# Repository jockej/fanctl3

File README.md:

# fanctl3
A simpler version of fanctl2

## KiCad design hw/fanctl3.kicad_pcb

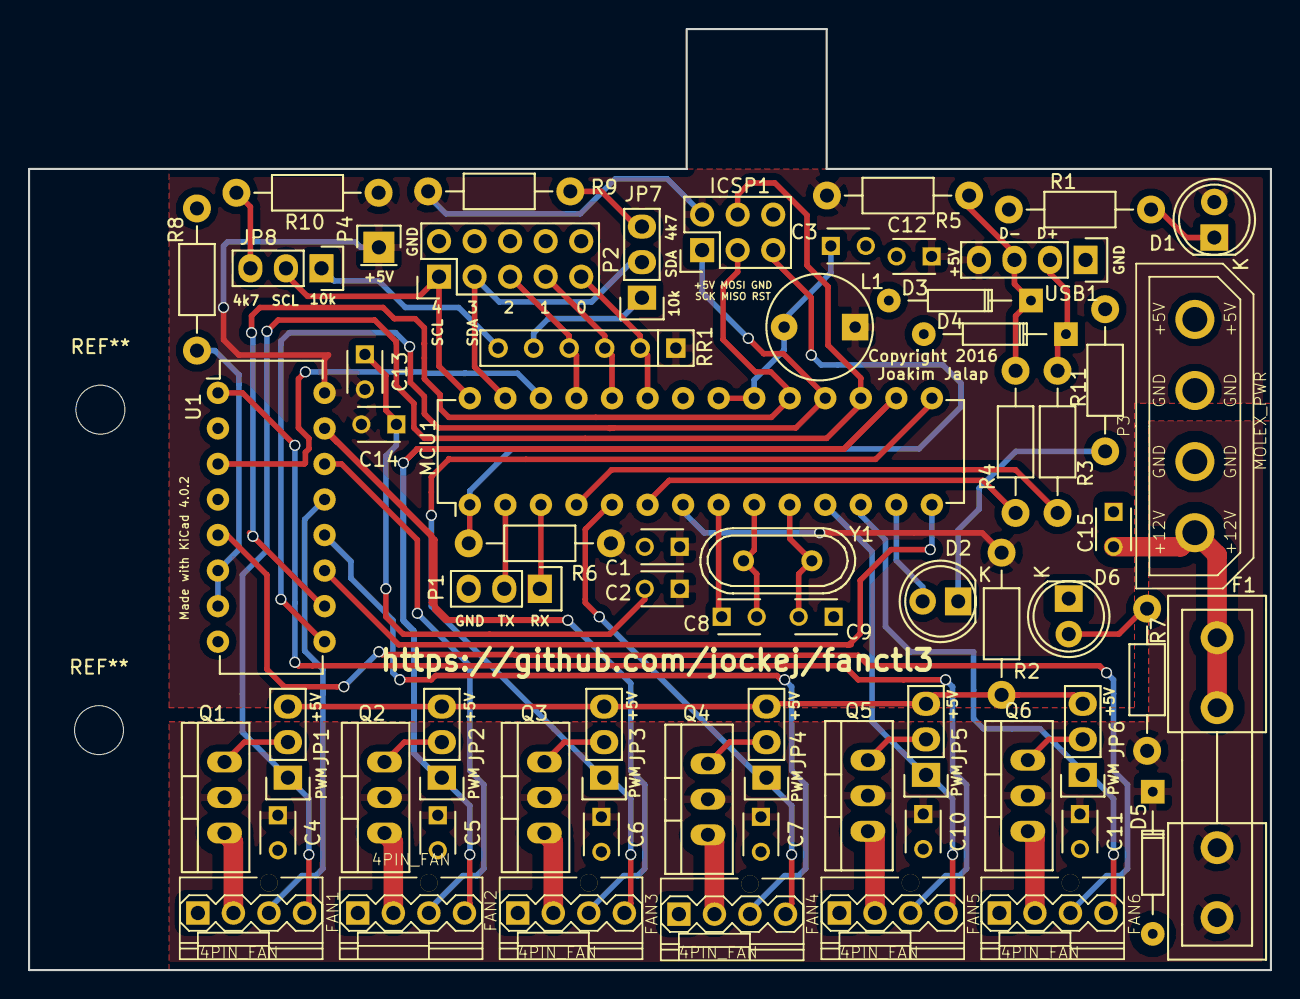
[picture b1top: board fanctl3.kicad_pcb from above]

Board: 2 copper layers, 88.8 x 67.2 mm, 64 parts (0 on the bottom side), 58 nets.

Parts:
C1, C3, C4, C5, C6, C7, C10, C11, C12, C13: 0.1u; C_Disc_D3_P2.5
C2, C14: 22n; C_Disc_D3_P2.5
C8, C9: 22p; C_Disc_D3_P2.5
C15: Decoupler; C_Disc_D3_P2.5
D1, D2, D6: LED; LED-5MM
D3, D4: ZENER; Diode_DO-35_SOD27_Horizontal_RM10
D5: D; Diode_DO-35_SOD27_Horizontal_RM10
F1: FUSE; Fuseholder5x20_horiz_open_inline_Type-I
FAN1, FAN2, FAN3, FAN4, FAN5, FAN6: 4PIN_FAN; AB2_HDR_M04-1V_CPU_FAN
ICSP1: Prog_con; Pin_Header_Straight_2x03
JP1, JP2, JP3, JP4, JP5, JP6, JP7, JP8: JUMPER3; Pin_Header_Straight_1x03
L1: 10uH; INDUCTOR_V
MCU1: ATMEGA168PA-P; DIP-28_W7.62mm
P1: CONN_01X03; Pin_Header_Straight_1x03
P2: CONN_02X05; Pin_Header_Straight_2x05
P3: MOLEX_PWR; AB2_ATX_PSU-4PIN-V
P4: CONN_01X01; Pin_Header_Straight_1x01
Q1, Q2, Q3, Q4, Q5, Q6: FAN_NMOS; TO-220_Neutral123_Vertical
R1, R5, R7, R8: FANCTL2_R; Resistor_Horizontal_RM10mm
R2, R6: 10K; Resistor_Horizontal_RM10mm
R3, R4: 68; Resistor_Horizontal_RM10mm
R9, R10: 4k7; Resistor_Horizontal_RM10mm
R11: R; Resistor_Horizontal_RM10mm
RR1: 10k; Resistor_Array_SIP6
U1: 4051; DIP-16_W7.62mm
USB1: USB_HDR; Pin_Header_Straight_1x04
Y1: Crystal_Small; Crystal_HC49-U_Vertical

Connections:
12VGND: C4.2, C5.2, C6.2, C7.2, C10.2, C11.2, C15.1, D5.2, D6.1, FAN1.1, FAN2.1, FAN3.1, FAN4.1, FAN5.1, FAN6.1, P3.2
+5V: C1.1, C2.1, C12.1, C13.2, C14.2, D1.2, ICSP1.2, L1.1, MCU1.7, P4.1, R2.1, R5.2, R6.1, R9.1, R10.1, RR1.1, U1.16, USB1.4
+12V: C4.1, C5.1, C6.1, C7.1, C10.1, C11.1, D5.1, F1.1, Q1.2, Q2.2, Q3.2, Q4.2, Q5.2, Q6.2, R7.1
COM5V: JP1.3, JP2.3, JP3.3, JP4.3, JP5.3, JP6.3, R2.2
GND: C1.2, C2.2, C3.2, C8.1, C9.1, C12.2, C13.1, C14.1, D3.2, D4.2, ICSP1.6, MCU1.8, MCU1.22, P1.3, P2.2, P2.4, P2.6, P2.8, P2.10, R1.2, R8.1, R11.2, U1.8, USB1.1
unnamed: C3.1, L1.2, MCU1.20, MCU1.21
unnamed: C8.2, MCU1.9, Y1.1
unnamed: C9.2, MCU1.10, Y1.2
unnamed: C15.2, F1.2, P3.1
unnamed: D1.1, R1.1
unnamed: D2.1, R11.1
unnamed: D2.2, MCU1.13
unnamed: D3.1, R4.1, R5.1, USB1.3
unnamed: D4.1, R3.1, USB1.2
unnamed: D6.2, R7.2
unnamed: FAN1.2, Q1.1
unnamed: FAN2.2, Q2.1
unnamed: FAN3.2, Q3.1
unnamed: FAN4.2, Q4.1
unnamed: FAN5.2, Q5.1
unnamed: FAN6.2, Q6.1
unnamed: ICSP1.5, MCU1.1, R6.2
unnamed: JP1.2, Q1.3
unnamed: JP2.2, Q2.3
unnamed: JP3.2, Q3.3
unnamed: JP4.2, Q4.3
unnamed: JP5.2, Q5.3
unnamed: JP6.2, Q6.3
unnamed: JP7.1, RR1.5
unnamed: JP7.3, R9.2
unnamed: JP8.1, RR1.6
unnamed: JP8.3, R10.2
unnamed: MCU1.2, P1.2
unnamed: MCU1.3, P1.1
unnamed: MCU1.4, R3.2
unnamed: MCU1.6, R4.2
unnamed: R8.2, U1.6, U1.7
PWM0: FAN1.4, ICSP1.4, JP1.1, MCU1.17
PWM1: FAN2.4, JP2.1, MCU1.16
PWM2: FAN3.4, JP3.1, MCU1.15
PWM3: FAN4.4, JP4.1, MCU1.5
PWM4: FAN5.4, JP5.1, MCU1.11
PWM5: FAN6.4, JP6.1, MCU1.12
SEL0: MCU1.14, U1.11
SEL1: ICSP1.3, MCU1.19, U1.10
SEL2: ICSP1.1, MCU1.18, U1.9
SENS0: MCU1.26, U1.3
TACH0: FAN1.3, U1.13
TACH1: FAN2.3, U1.14
TACH2: FAN3.3, U1.15
TACH3: FAN4.3, U1.12
TACH4: FAN5.3, U1.1
TACH5: FAN6.3, U1.5
TEMP0: MCU1.23, P2.9, RR1.2
TEMP1: MCU1.24, P2.7, RR1.3
TEMP2: MCU1.25, P2.5, RR1.4
TEMP3/SDA: JP7.2, MCU1.27, P2.3
TEMP4/SCL: JP8.2, MCU1.28, P2.1

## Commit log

2016-07-02 Schematics
2016-08-07 Add a resistor array I'm not gonna use anyway...
2016-08-07 Add i2c port and a resistor for the LED.
2016-08-07 A picture and a pdf schematic.

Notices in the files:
hw/fanctl3.kicad_pcb:
Copyright 2016
